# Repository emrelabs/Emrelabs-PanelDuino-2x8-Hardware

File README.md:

# emrelabs PanelDuino-2x8 Hardware

Please support us:
https://www.tindie.com/products/emrelabs/panelduino-2x8-smart-display/

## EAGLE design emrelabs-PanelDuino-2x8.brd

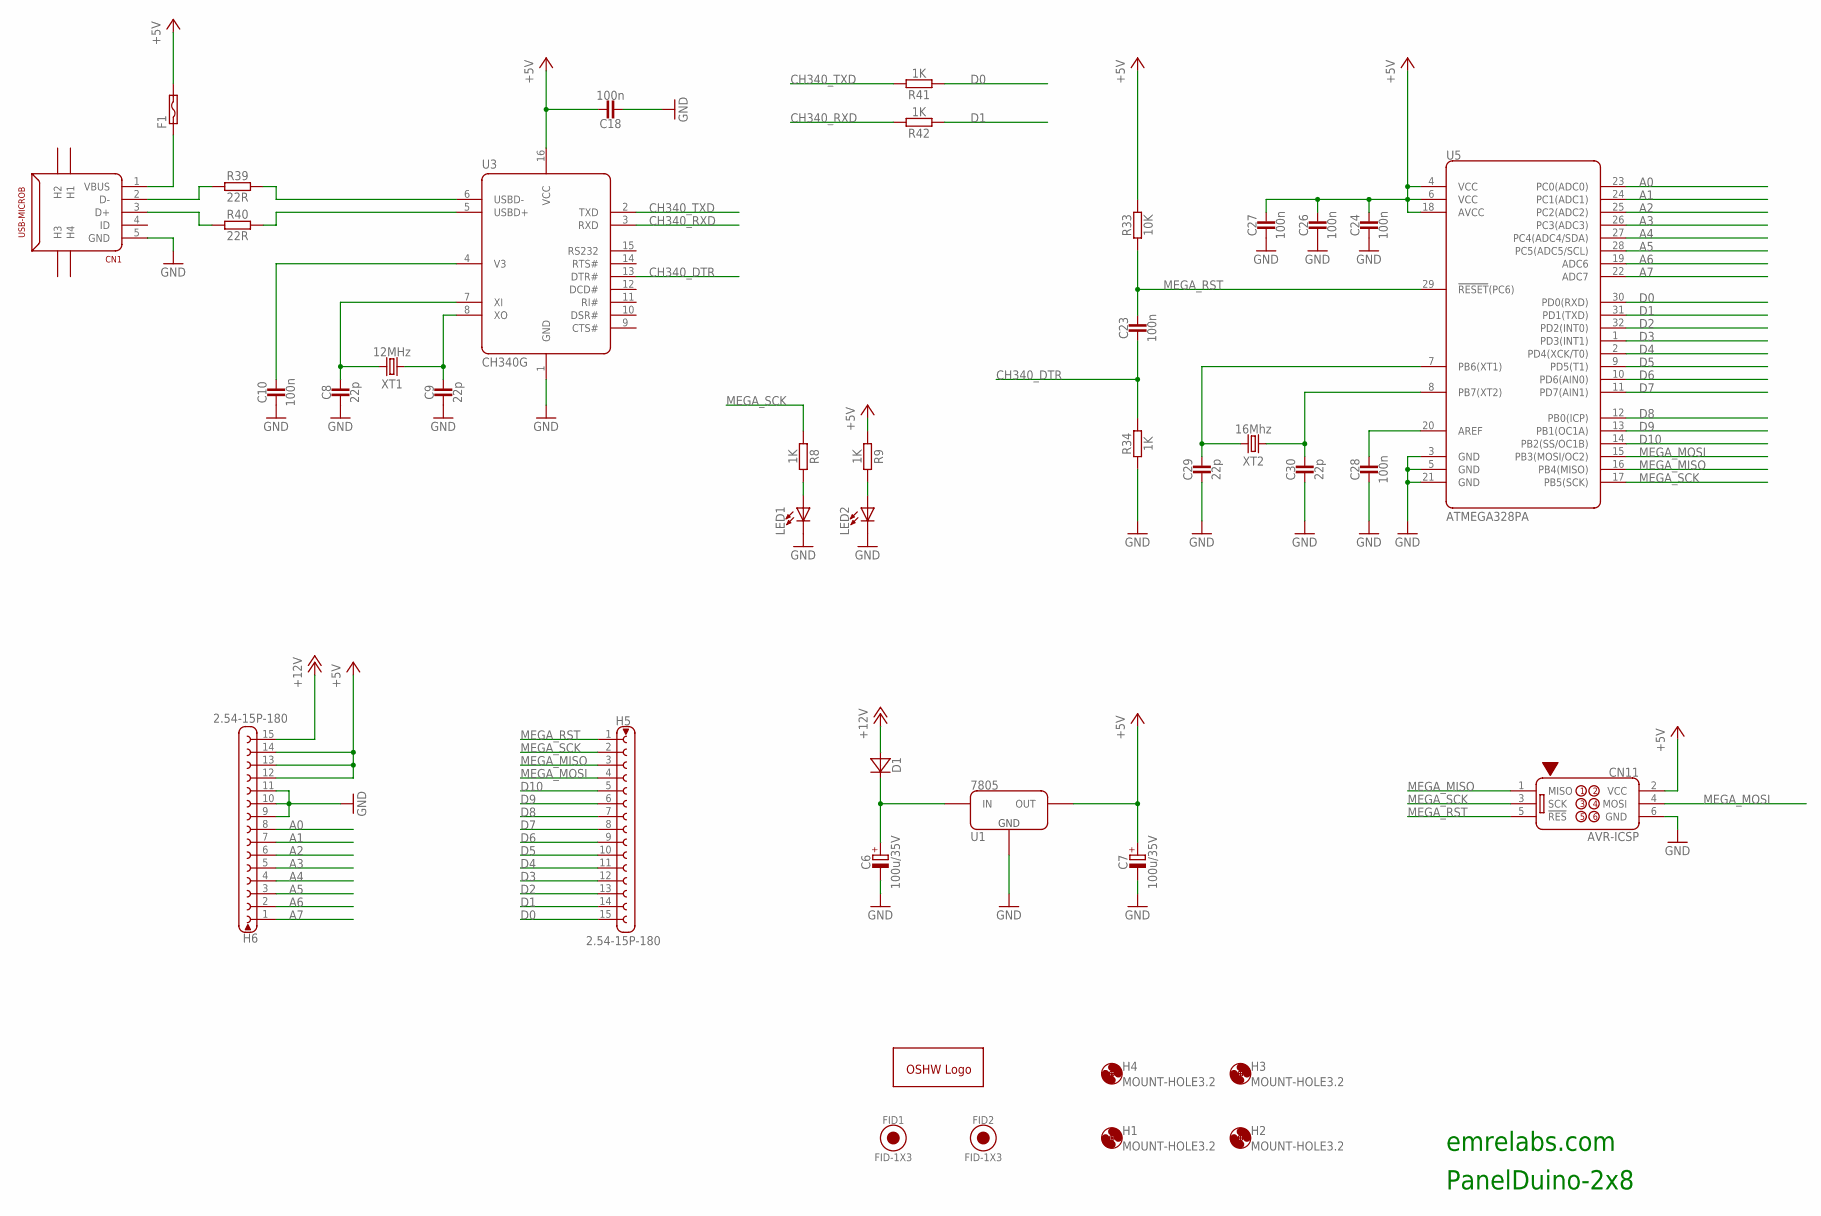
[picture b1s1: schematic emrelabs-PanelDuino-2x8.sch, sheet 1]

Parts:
C6, C7: 100u/35V; ALU-SIZE-D
C8, C9, C29, C30: 22p; C1206
C10, C18, C23, C24, C26, C27, C28: 100n; C1206
CN1: USB-MICROB; USB-MICRO-B
CN11: AVR-ICSP
D1: D-DO214AC; DO214AC
F1: FUSE-PTC-1206; F1206
FID1, FID2: FID-1X3; FIDUCIAL-1X3MM
H1, H2, H3, H4: MOUNT-HOLE3.2; 3,2
H5, H6: 2.54-15P-180; 2.54-15P
LED1, LED2: LED-1206; LED1206
LOGO1: OSHWLOGOLOGO5MM; OSHW_5MM
R8, R9, R34, R41, R42: 1K; R1206
R33: 10K; R1206
R39, R40: 22R; R1206
U1: 7805; DPAK
U3: CH340G; SOIC-16
U5: ATMEGA328PA; TQFP32-6X6-P0.8
XT1: 12MHz; XT-HC49
XT2: 16Mhz; XT-HC49

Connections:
+5V: C7.+, C18.1, C24.1, C26.1, C27.1, CN11.2 (VCC), F1.2, H6.12, H6.13, H6.14, R9.1, R33.2, U1.3 (OUT), U3.16 (VCC), U5.4 (VCC), U5.6 (VCC), U5.18 (AVCC); also elsewhere on the board
+12V: D1.A, H6.15
A0: H6.8, U5.23 (PC0(ADC0))
A1: H6.7, U5.24 (PC1(ADC1))
A2: H6.6, U5.25 (PC2(ADC2))
A3: H6.5, U5.26 (PC3(ADC3))
A4: H6.4, U5.27 (PC4(ADC4/SDA)); also elsewhere on the board
A5: H6.3, U5.28 (PC5(ADC5/SCL)); also elsewhere on the board
A6: H6.2, U5.19 (ADC6)
A7: H6.1, U5.22 (ADC7)
CH340_DTR: C23.2, R34.2, U3.13 (DTR#)
CH340_RXD: R42.2, U3.3 (RXD)
CH340_TXD: R41.2, U3.2 (TXD)
D0: H5.15, R41.1, U5.30 (PD0(RXD))
D1: H5.14, R42.1, U5.31 (PD1(TXD))
D2: H5.13, U5.32 (PD2(INT0))
D3: H5.12, U5.1 (PD3(INT1))
D4: H5.11, U5.2 (PD4(XCK/T0))
D5: H5.10, U5.9 (PD5(T1))
D6: H5.9, U5.10 (PD6(AIN0))
D7: H5.8, U5.11 (PD7(AIN1))
D8: H5.7, U5.12 (PB0(ICP))
D9: H5.6, U5.13 (PB1(OC1A))
D10: H5.5, U5.14 (PB2(SS/OC1B))
GND: C6.-, C7.-, C8.2, C9.2, C10.2, C18.2, C24.2, C26.2, C27.2, C28.2, C29.2, C30.2, CN1.5 (GND), CN11.6 (GND), H6.9, H6.10, H6.11, LED1.C, LED2.C, R34.1, U1.4 (GND), U3.1 (GND), U5.3 (GND), U5.5 (GND), U5.21 (GND); also elsewhere on the board
MEGA_MISO: CN11.1 (MISO), H5.3, U5.16 (PB4(MISO))
MEGA_MOSI: CN11.4 (MOSI), H5.4, U5.15 (PB3(MOSI/OC2))
MEGA_RST: C23.1, CN11.5 (!RES!), H5.1, R33.1, U5.29 (!RESET!(PC6))
MEGA_SCK: CN11.3 (SCK), H5.2, R8.1, U5.17 (PB5(SCK))
unnamed: C6.+, D1.C, U1.1 (IN)
unnamed: C10.1, U3.4 (V3)
unnamed: LED1.A, R8.2
unnamed: LED2.A, R9.2
unnamed: CN1.1 (VBUS), F1.1
unnamed: C28.1, U5.20 (AREF)
unnamed: C30.1, U5.8 (PB7(XT2)), XT2.1
unnamed: C9.1, U3.8 (XO), XT1.1
unnamed: C8.1, U3.7 (XI), XT1.2
unnamed: C29.1, U5.7 (PB6(XT1)), XT2.2
unnamed: CN1.2 (D-), R39.1
unnamed: CN1.3 (D+), R40.1
unnamed: R39.2, U3.6 (USBD-)
unnamed: R40.2, U3.5 (USBD+)

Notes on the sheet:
PanelDuino-2x8
emrelabs.com

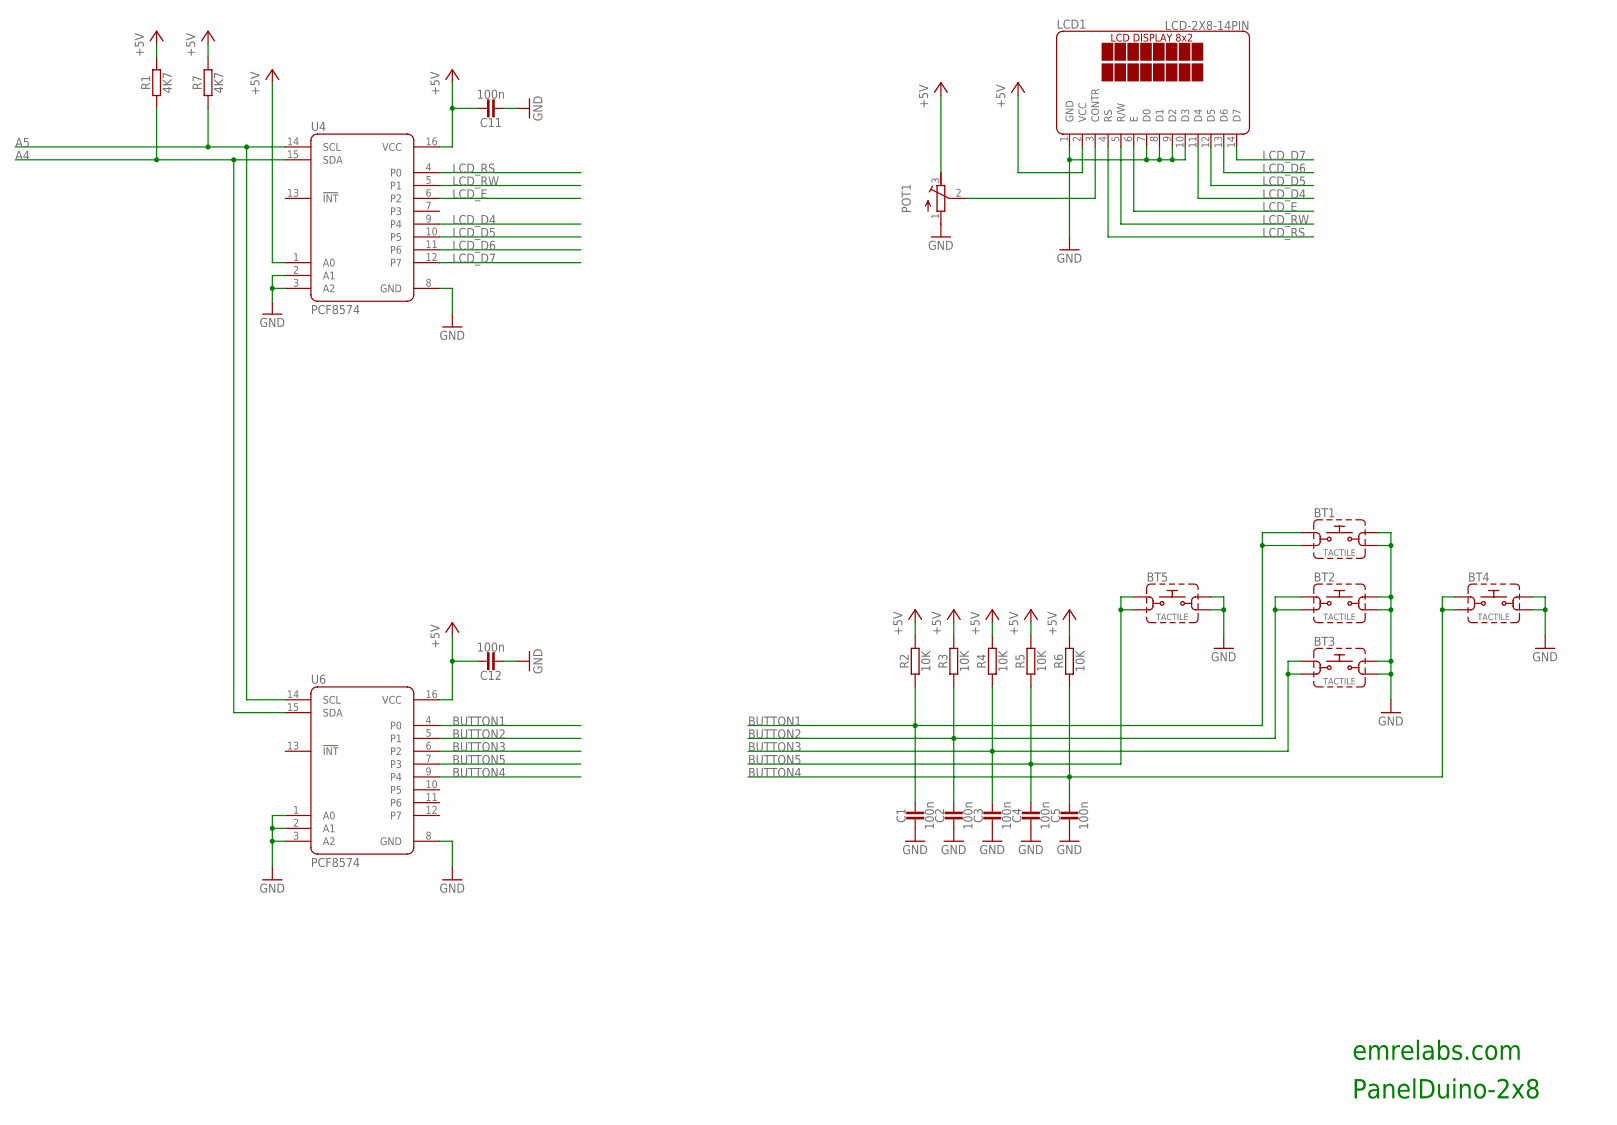
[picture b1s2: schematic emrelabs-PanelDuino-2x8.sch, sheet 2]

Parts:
BT1, BT2, BT3, BT4, BT5: TACTILE; TACTILE-6X6-DIP
C1, C2, C3, C4, C5, C11, C12: 100n; C1206
LCD1: LCD-2X8-14PIN; 2X8-LCD-14PIN
POT1: R-TRIM-5X4.5MM
R1, R7: 4K7; R1206
R2, R3, R4, R5, R6: 10K; R1206
U4, U6: PCF8574; SOIC-16W

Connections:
+5V: C11.1, C12.1, LCD1.2 (VCC), POT1.3 (E), R1.2, R2.2, R3.2, R4.2, R5.2, R6.2, R7.2, U4.1 (A0), U4.16 (VCC), U6.16 (VCC); also elsewhere on the board
A4: R1.1, U4.15 (SDA), U6.15 (SDA); also elsewhere on the board
A5: R7.1, U4.14 (SCL), U6.14 (SCL); also elsewhere on the board
BUTTON1: BT1.1A, BT1.1B, C1.1, R2.1, U6.4 (P0)
BUTTON2: BT2.1A, BT2.1B, C2.1, R3.1, U6.5 (P1)
BUTTON3: BT3.1A, BT3.1B, C3.1, R4.1, U6.6 (P2)
BUTTON4: BT4.1A, BT4.1B, C5.1, R6.1, U6.9 (P4)
BUTTON5: BT5.1A, BT5.1B, C4.1, R5.1, U6.7 (P3)
GND: BT1.2A, BT1.2B, BT2.2A, BT2.2B, BT3.2A, BT3.2B, BT4.2A, BT4.2B, BT5.2A, BT5.2B, C1.2, C2.2, C3.2, C4.2, C5.2, C11.2, C12.2, LCD1.1 (GND), LCD1.7 (D0), LCD1.8 (D1), LCD1.9 (D2), LCD1.10 (D3), POT1.1 (A), U4.2 (A1), U4.3 (A2), U4.8 (GND), U6.1 (A0), U6.2 (A1), U6.3 (A2), U6.8 (GND); also elsewhere on the board
LCD_D4: LCD1.11 (D4), U4.9 (P4)
LCD_D5: LCD1.12 (D5), U4.10 (P5)
LCD_D6: LCD1.13 (D6), U4.11 (P6)
LCD_D7: LCD1.14 (D7), U4.12 (P7)
LCD_E: LCD1.6 (E), U4.6 (P2)
LCD_RS: LCD1.4 (RS), U4.4 (P0)
LCD_RW: LCD1.5 (R/W), U4.5 (P1)
unnamed: LCD1.3 (CONTR), POT1.2 (S)

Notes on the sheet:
PanelDuino-2x8
emrelabs.com

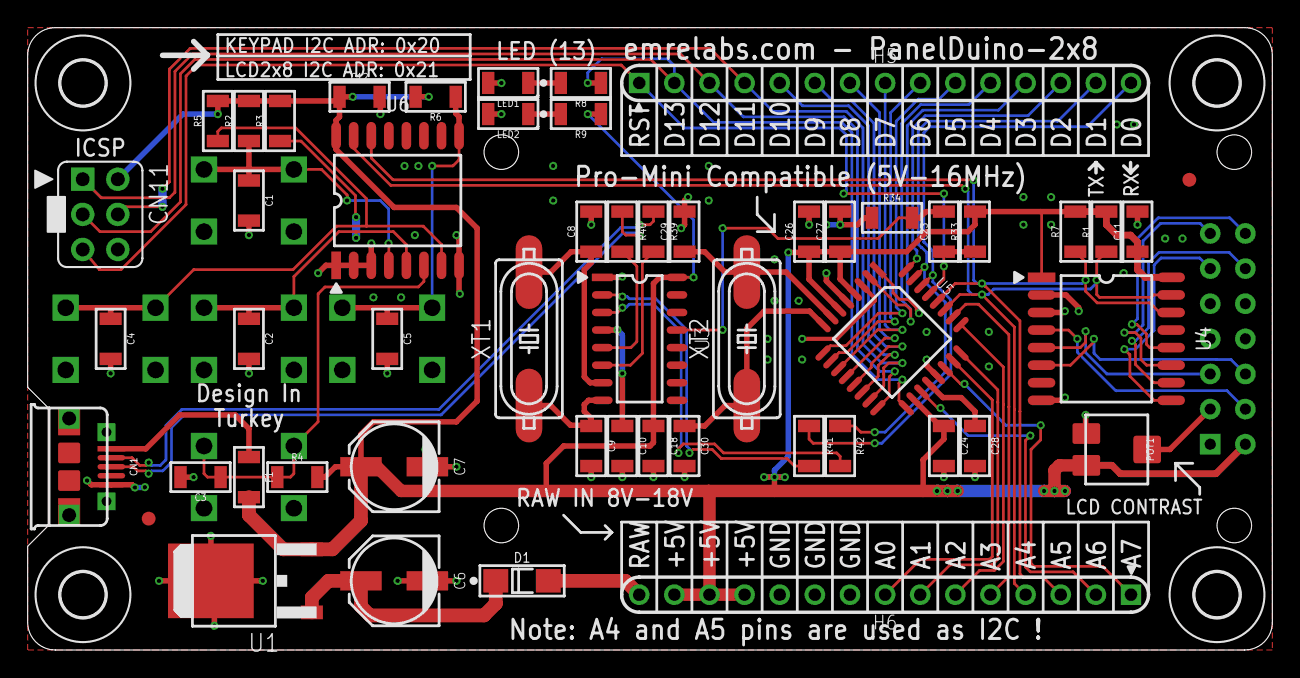
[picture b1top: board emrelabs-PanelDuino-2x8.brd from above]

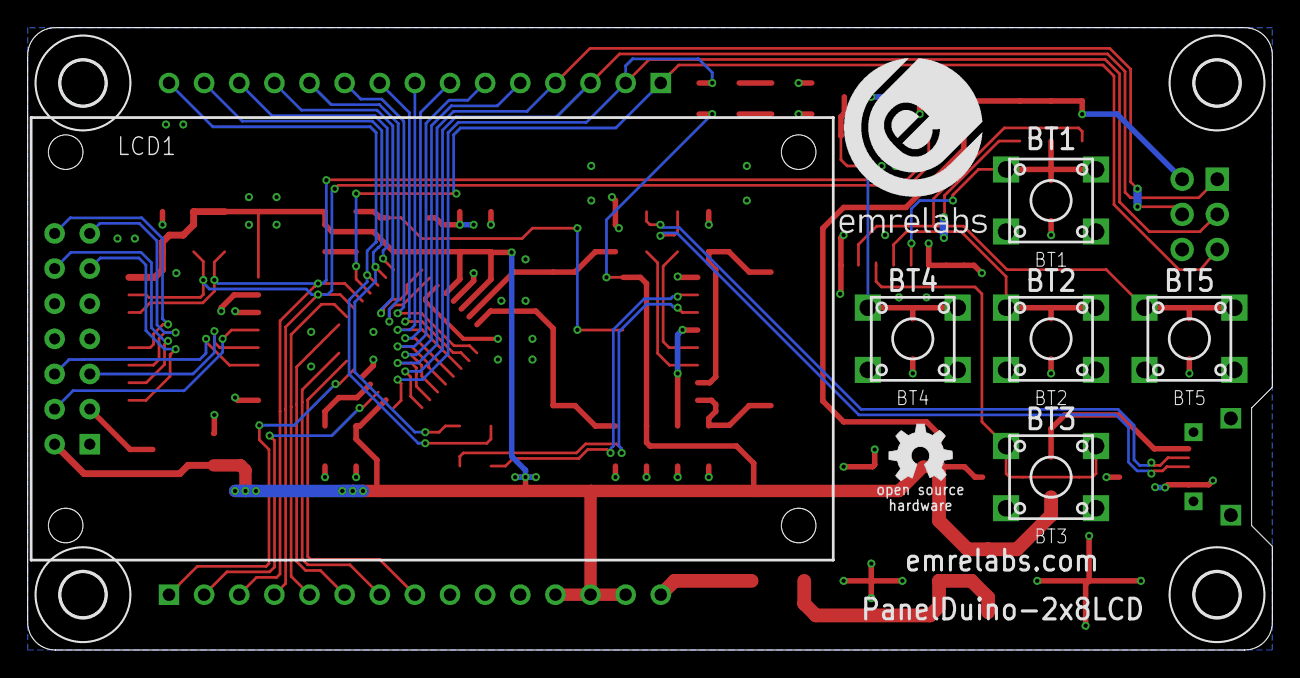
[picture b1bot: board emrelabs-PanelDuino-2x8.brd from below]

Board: 2 copper layers, 90.0 x 45.0 mm, 64 parts (7 on the bottom side), 56 nets.

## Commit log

2018-06-04 Crystal value updated
